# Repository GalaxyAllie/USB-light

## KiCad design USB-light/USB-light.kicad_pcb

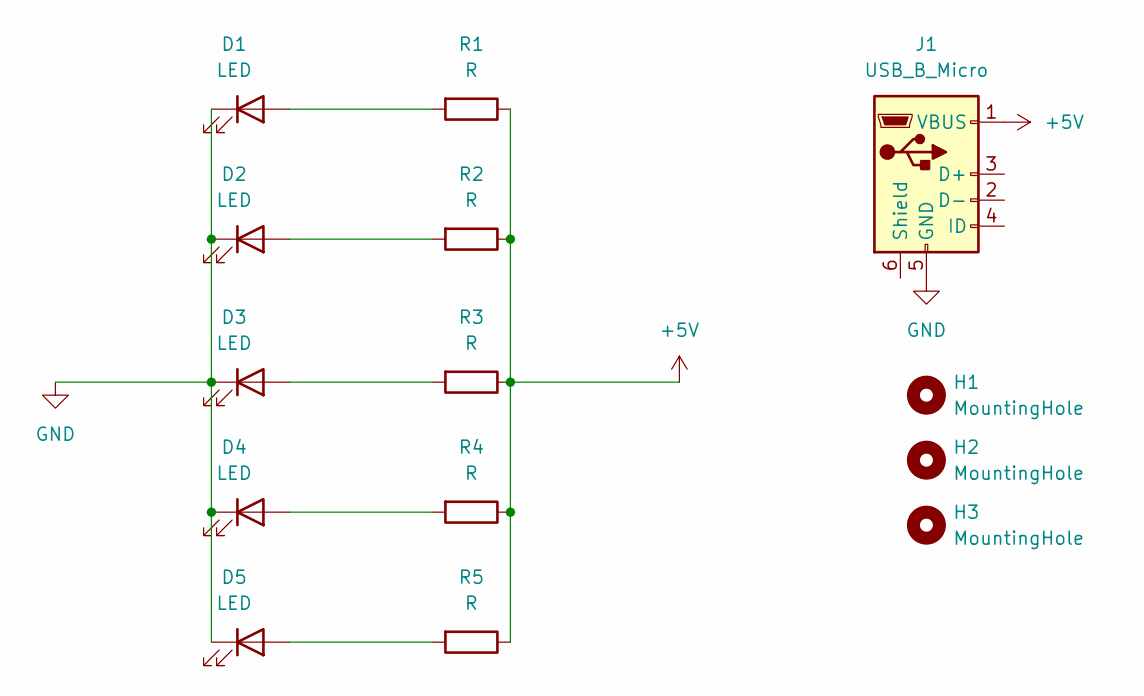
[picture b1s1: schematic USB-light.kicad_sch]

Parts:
D1, D2, D3, D4, D5: LED; LED_PLCC_2835_Handsoldering
H1, H2, H3: MountingHole; MountingHole_2.2mm_M2
J1: USB_B_Micro; USB_Micro-B_GCT_USB3076-30-A
R1, R2, R3, R4, R5: R; R_1210_3225Metric_Pad1.30x2.65mm_HandSolder

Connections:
+5V: J1.1 (VBUS), R1.1, R2.1, R3.1, R4.1, R5.1
GND: D1.1 (K), D2.1 (K), D3.1 (K), D4.1 (K), D5.1 (K), J1.5 (GND)
unnamed: D1.2 (A), R1.2
unnamed: D2.2 (A), R2.2
unnamed: D3.2 (A), R3.2
unnamed: D4.2 (A), R4.2
unnamed: D5.2 (A), R5.2

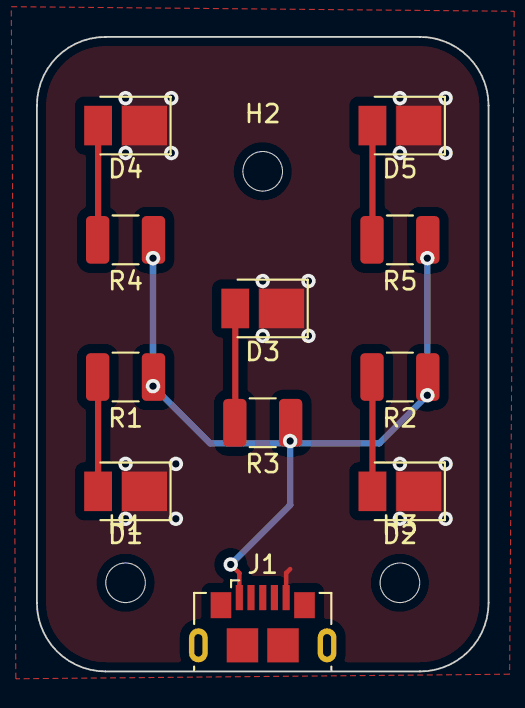
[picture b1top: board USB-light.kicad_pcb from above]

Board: 2 copper layers, 25.1 x 35.3 mm, 14 parts (0 on the bottom side), 7 nets.

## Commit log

2022-01-15 schematic
2022-01-16 Board layout
